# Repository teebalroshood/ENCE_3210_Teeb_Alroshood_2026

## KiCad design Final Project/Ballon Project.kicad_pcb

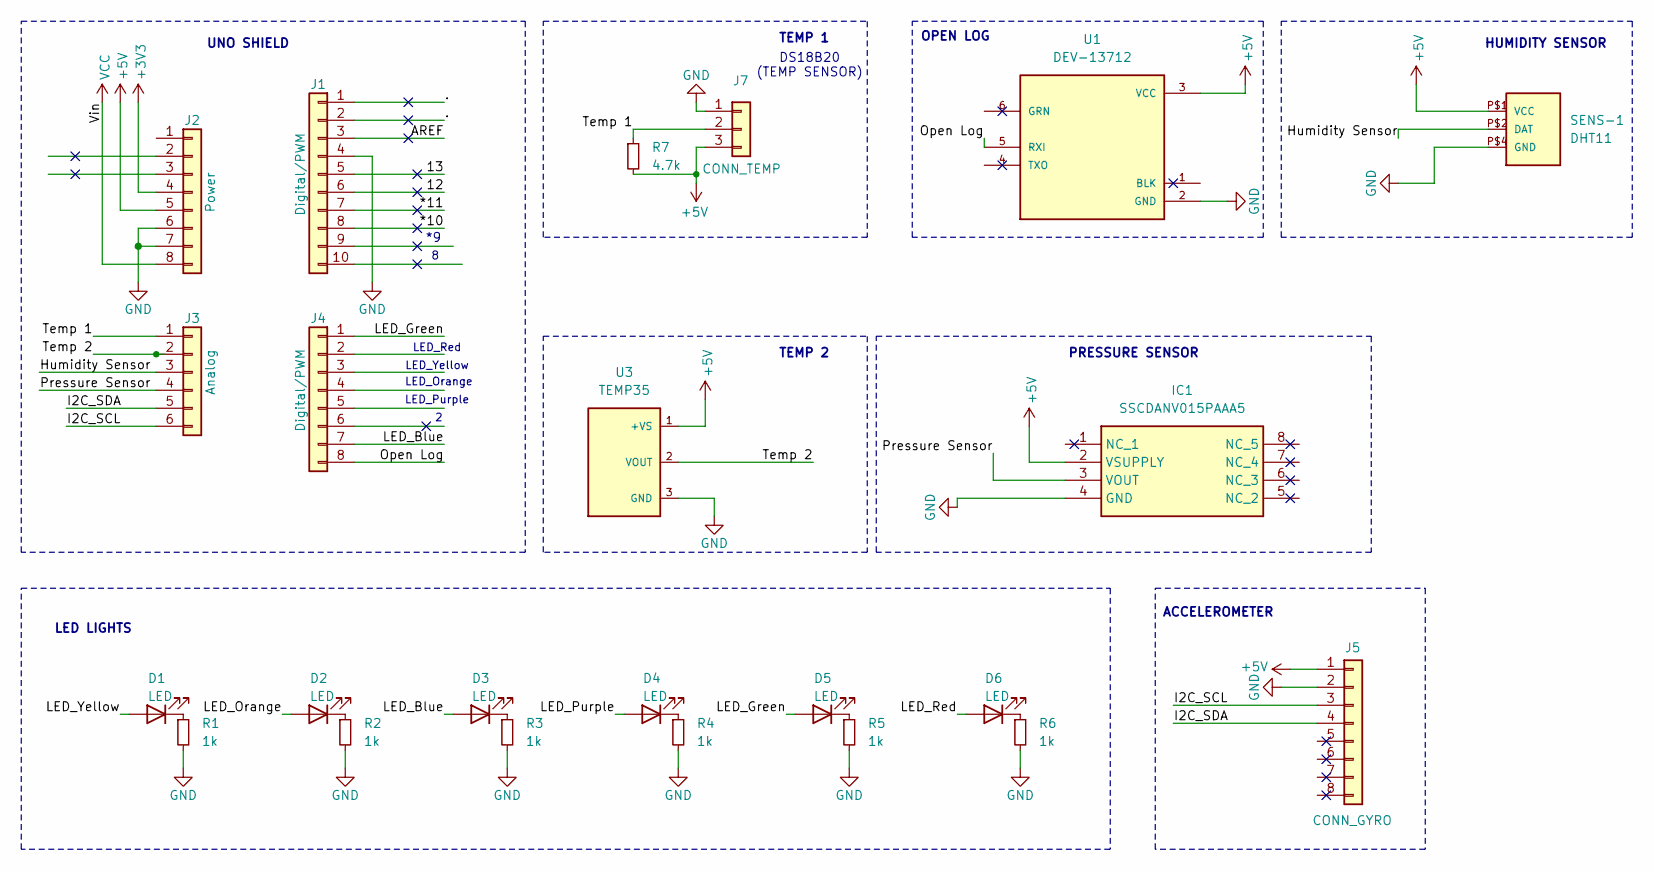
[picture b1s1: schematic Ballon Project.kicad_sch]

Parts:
D1, D2, D3, D4, D5, D6: LED; LED_D5.0mm
IC1: SSCDANV015PAAA5; Mouser Part Number 785-SSCDANV015PAAA5
J1: Digital/PWM; PinSocket_1x10_P2.54mm_Vertical
J2: Power; PinSocket_1x08_P2.54mm_Vertical
J3: Analog; PinSocket_1x06_P2.54mm_Vertical
J4: Digital/PWM; PinSocket_1x08_P2.54mm_Vertical
J5: CONN_GYRO; PinSocket_1x08_P2.54mm_Vertical
J7: CONN_TEMP; JST_XH_B3B-XH-A_1x03_P2.50mm_Vertical
R1, R2, R3, R4, R5, R6: 1k; R_Axial_DIN0411_L9.9mm_D3.6mm_P15.24mm_Horizontal
R7: 4.7k; R_Axial_DIN0411_L9.9mm_D3.6mm_P15.24mm_Horizontal
SENS-1: DHT11; SENSOR-DHT11
U1: DEV-13712; MODULE_DEV-13712
U3: TEMP35; XDCR_TMP36GT9

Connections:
+3V3: J2.4
+5V: IC1.2 (VSUPPLY), J2.5, J5.1, J7.3, R7.2, SENS-1.P$1 (VCC), U1.3 (VCC), U3.1 (+VS)
/12: J1.6
/13: J1.5
/*10: J1.8
/*11: J1.7
/.: J1.1, J1.2
/AREF: J1.3
/Humidity Sensor: J3.3, SENS-1.P$2 (DAT)
/I2C_SCL: J3.6, J5.3
/I2C_SDA: J3.5, J5.4
/LED_Blue: D3.2 (A), J4.7
/LED_BlueTwo: D4.2 (A)
/LED_Green: D5.2 (A), J4.1
/LED_Orange: D2.2 (A)
/LED_Red: D6.2 (A)
/LED_Yellow: D1.2 (A)
/Open Log: J4.8, U1.5 (RXI)
/Pressure Sensor: IC1.3 (VOUT), J3.4
/Temp 1: J3.1, J7.2, R7.1
/Temp 2: J3.2, U3.2 (VOUT)
GND: IC1.4 (GND), J1.4, J2.6, J2.7, J5.2, J7.1, R1.2, R2.2, R3.2, R4.2, R5.2, R6.2, SENS-1.P$4 (GND), U1.2 (GND), U3.3 (GND)
unnamed: D1.1 (K), R1.1
unnamed: D2.1 (K), R2.1
unnamed: D3.1 (K), R3.1
unnamed: D4.1 (K), R4.1
unnamed: D5.1 (K), R5.1
unnamed: D6.1 (K), R6.1
VCC: J2.8

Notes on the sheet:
UNO SHIELD
LED_Purple
ACCELEROMETER
TEMP 1
LED_Yellow
TEMP 2
PRESSURE SENSOR
HUMIDITY SENSOR
LED_Orange
LED LIGHTS
OPEN LOG
DS18B20 (TEMP SENSOR)
LED_Red

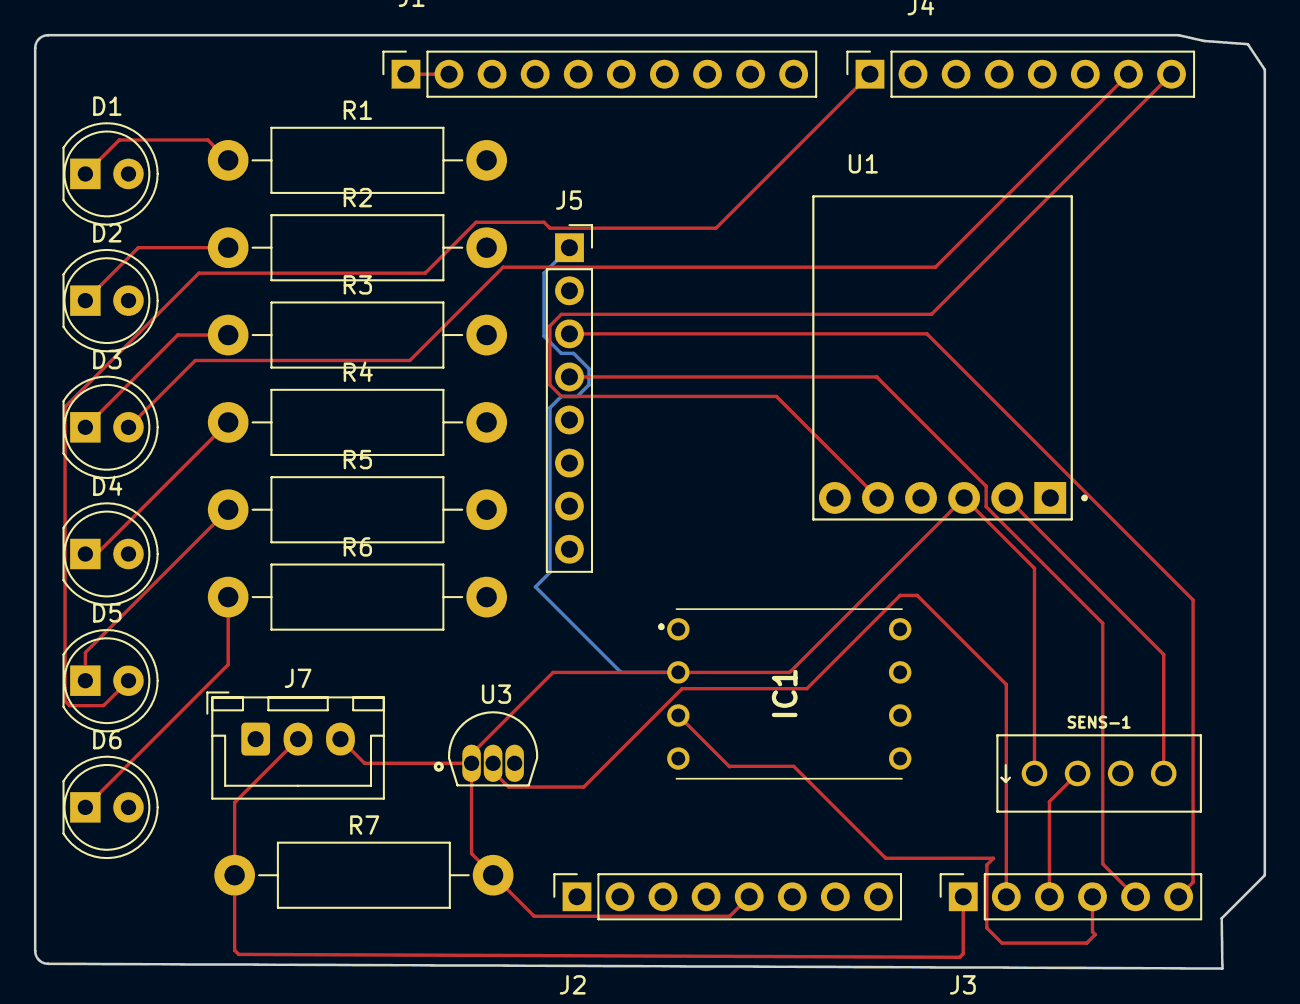
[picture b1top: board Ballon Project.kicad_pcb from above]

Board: 2 copper layers, 72.5 x 55.0 mm, 23 parts (0 on the bottom side), 18 nets.

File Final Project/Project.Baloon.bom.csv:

"Id";"Designator";"Footprint";"Quantity";"Designation";"Supplier and ref";
1;"J4";"PinSocket_1x08_P2.54mm_Vertical";1;"Digital/PWM";;;
2;"IC1";"SSCDANV015PAAA5";1;"SSCDANV015PAAA5";;;
3;"R1,R6,R3,R5,R4,R2";"R_Axial_DIN0411_L9.9mm_D3.6mm_P15.24mm_Horizontal";6;"1k";;;
4;"D4,D6,D5,D2,D1,D3";"LED_D5.0mm";6;"LED";;;
5;"U1";"MODULE_DEV-13712";1;"DEV-13712";;;
6;"J1";"PinSocket_1x10_P2.54mm_Vertical";1;"Digital/PWM";;;
7;"J5";"PinSocket_1x08_P2.54mm_Vertical";1;"CONN_GYRO";;;
8;"J3";"PinSocket_1x06_P2.54mm_Vertical";1;"Analog";;;
9;"J2";"PinSocket_1x08_P2.54mm_Vertical";1;"Power";;;
10;"SENS-1";"SENSOR-DHT11";1;"DHT11";;;
11;"U3";"XDCR_TMP36GT9";1;"TEMP35";;;
12;"J7";"JST_XH_B3B-XH-A_1x03_P2.50mm_Vertical";1;"CONN_TEMP";;;

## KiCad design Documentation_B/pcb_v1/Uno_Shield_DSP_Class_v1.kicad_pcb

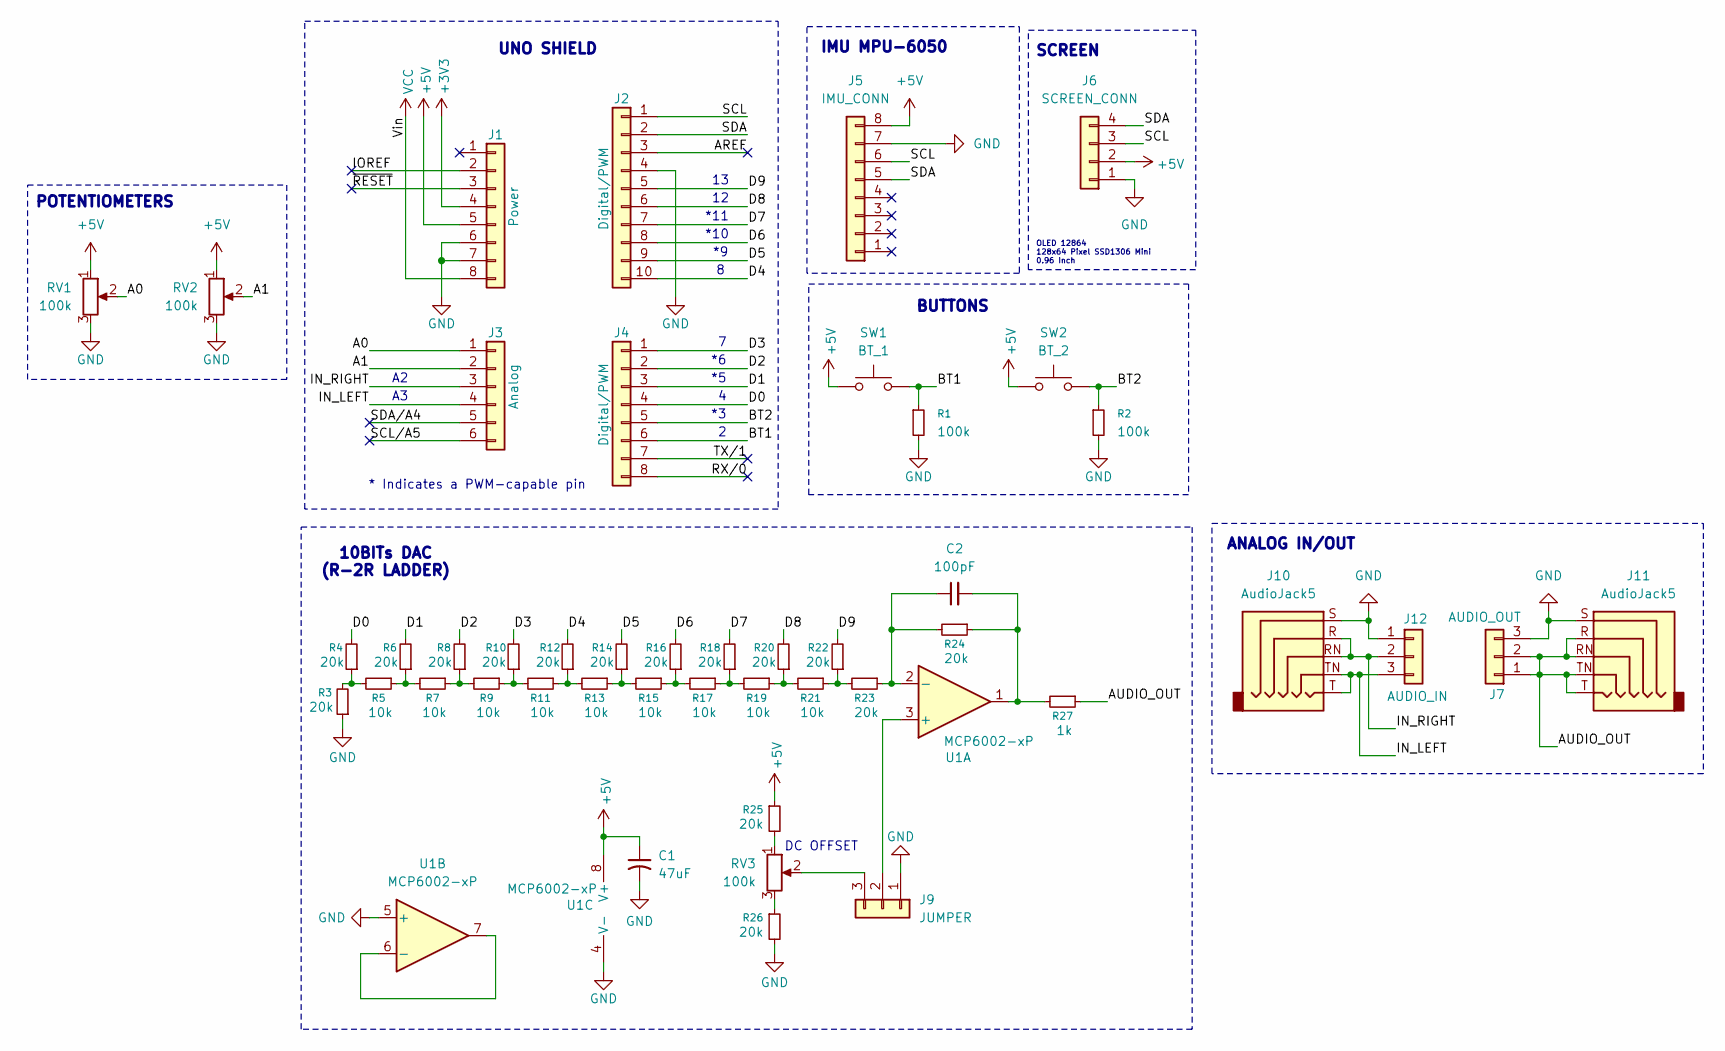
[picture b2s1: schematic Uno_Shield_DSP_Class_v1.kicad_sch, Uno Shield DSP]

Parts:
C1: 47uF; CP_Radial_D6.3mm_P2.50mm
C2: 100pF; C_Disc_D5.0mm_W2.5mm_P2.50mm
J1: Power; PinSocket_1x08_P2.54mm_Vertical
J2: Digital/PWM; PinSocket_1x10_P2.54mm_Vertical
J3: Analog; PinSocket_1x06_P2.54mm_Vertical
J4: Digital/PWM; PinSocket_1x08_P2.54mm_Vertical
J5: IMU_CONN; PinSocket_1x08_P2.54mm_Vertical
J6: SCREEN_CONN; PinHeader_1x04_P2.54mm_Vertical
J7: AUDIO_OUT; PinHeader_1x03_P2.54mm_Vertical
J9: JUMPER; PinHeader_1x03_P2.54mm_Vertical
J10, J11: AudioJack5; Jack_3.5mm_CUI_SJ1-3525N_Horizontal
J12: AUDIO_IN; PinHeader_1x03_P2.54mm_Vertical
R1, R2: 100k; R_Axial_DIN0309_L9.0mm_D3.2mm_P2.54mm_Vertical
R3, R4, R6, R8, R10, R12, R14, R16, R18, R20, R22, R23, R24, R25, R26: 20k; R_Axial_DIN0309_L9.0mm_D3.2mm_P2.54mm_Vertical
R5, R7, R9, R11, R13, R15, R17, R19, R21: 10k; R_Axial_DIN0309_L9.0mm_D3.2mm_P2.54mm_Vertical
R27: 1k; R_Axial_DIN0309_L9.0mm_D3.2mm_P2.54mm_Vertical
RV1, RV2, RV3: 100k; Potentiometer_Bourns_3386P_Vertical
SW1: BT_1; SW_PUSH_6mm
SW2: BT_2; SW_PUSH_6mm
U1: MCP6002-xP; DIP-8_W7.62mm_Socket_LongPads

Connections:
+3V3: J1.4
+5V: C1.1, J1.5, J5.8, J6.2, R25.1, RV1.1, RV2.1, SW1.1, SW2.1, U1.8 (V+)
/A0: J3.1, RV1.2
/A1: J3.2, RV2.2
/AREF: J2.3
/AUDIO_OUT: J7.1, J7.2, J11.R, J11.RN, J11.T, J11.TN, R27.1
/BT1: J4.6, R1.1, SW1.2
/BT2: J4.5, R2.1, SW2.2
/D0: J4.4, R4.2
/D1: J4.3, R6.2
/D2: J4.2, R8.2
/D3: J4.1, R10.2
/D4: J2.10, R12.2
/D5: J2.9, R14.2
/D6: J2.8, R16.2
/D7: J2.7, R18.2
/D8: J2.6, R20.2
/D9: J2.5, R22.2
/IN_LEFT: J3.4, J10.T, J10.TN, J12.3
/IN_RIGHT: J3.3, J10.R, J10.RN, J12.2
/IOREF: J1.2
/RX/0: J4.8
/SCL: J2.1, J5.6, J6.3
/SCL/A5: J3.6
/SDA: J2.2, J5.5, J6.4
/SDA/A4: J3.5
/TX/1: J4.7
/~RESET: J1.3
GND: C1.2, J1.6, J1.7, J2.4, J5.7, J6.1, J7.3, J9.1, J10.S, J11.S, J12.1, R1.2, R2.2, R3.1, R26.2, RV1.3, RV2.3, U1.4 (V-), U1.5 (+)
unnamed: C2.2, R24.1, R27.2, U1.1
unnamed: J9.2, U1.3 (+)
unnamed: J9.3, RV3.2
unnamed: R3.2, R4.1, R5.2
unnamed: R5.1, R6.1, R7.2
unnamed: R7.1, R8.1, R9.2
unnamed: R9.1, R10.1, R11.2
unnamed: R11.1, R12.1, R13.2
unnamed: R13.1, R14.1, R15.2
unnamed: R15.1, R16.1, R17.2
unnamed: R17.1, R18.1, R19.2
unnamed: R19.1, R20.1, R21.2
unnamed: R21.1, R22.1, R23.2
unnamed: R25.2, RV3.1
unnamed: R26.1, RV3.3
unnamed: C2.1, R23.1, R24.2, U1.2 (-)
unnamed: U1.6 (-), U1.7
VCC: J1.8

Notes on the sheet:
BUTTONS
IMU MPU-6050
POTENTIOMETERS
*11
DC OFFSET
10BITs DAC (R-2R LADDER)
ANALOG IN/OUT
*10
OLED 12864 128x64 Pixel SSD1306 Mini 0.96 Inch
* Indicates a PWM-capable pin
SCREEN
UNO SHIELD

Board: 2 copper layers, 46 parts (2 on the bottom side), 38 nets, no tracks yet.

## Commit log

2026-01-12 Create C_exercise
2026-01-15 Create Lab_1_exercises
2026-01-16 Lab2_Q1
2026-01-16 Lab2_Q2
2026-01-23 Create Lab4_Q4
2026-01-29 Create Lab_3
2026-02-04 Create Documentation_B
2026-02-04 Create code
2026-03-02 Create Documentation_C
2026-03-03 Create docs
2026-03-03 Create BOM
2026-03-03 Rename Screenshot 2026-01-29 at 9.51.08 PM.png to DAC Prototype
2026-03-03 Rename IMG_7094.MOV to DAC.oscilloscope
